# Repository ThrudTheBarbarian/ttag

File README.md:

# ttag
JTAG adapter for the Trion FPGAs. Accepts an FTDI mini-module which saves having to
embed an FTDI chip onto every board.

Exposes the SPI lines for programming SPI flash devices, and the JTAG lines for the FPGA.

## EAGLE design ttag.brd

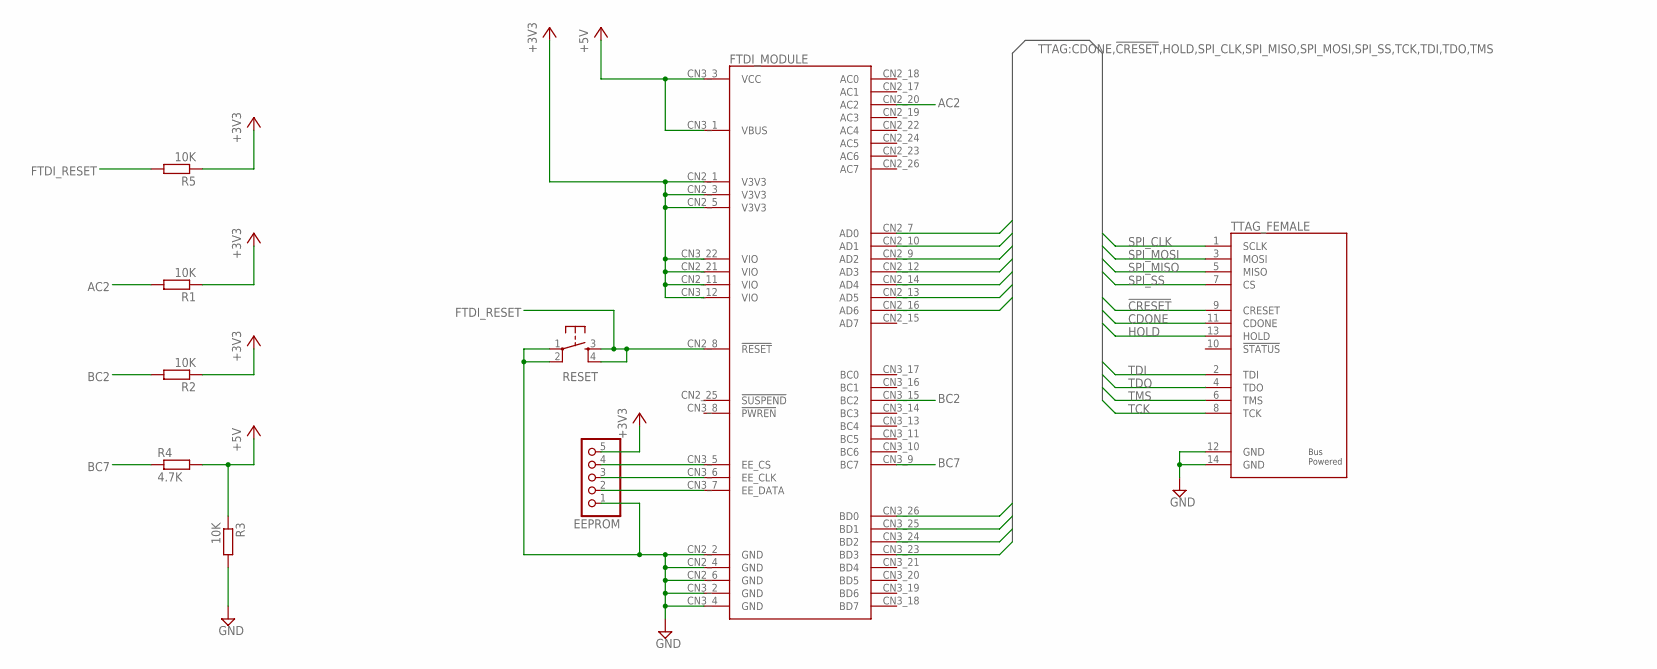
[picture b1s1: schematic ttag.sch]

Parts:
EEPROM: PINHD-1X05_2.54; 1X05
FTDI_MODULE: FTDI_MODULE
R1, R2, R3, R5: 10K; M1206
R4: 4.7K; M1206
RESET: TAC_SWITCHPTH; TACTILE-PTH
TTAG_FEMALE: TTAG_F; SFH11PBPCD07RABK

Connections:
!CRESET!: FTDI_MODULE.CN2_14 (AD4), TTAG_FEMALE.9 (CRESET)
+3V3: EEPROM.5, FTDI_MODULE.CN2_1 (V3V3), FTDI_MODULE.CN2_3 (V3V3), FTDI_MODULE.CN2_5 (V3V3), FTDI_MODULE.CN2_11 (VIO), FTDI_MODULE.CN2_21 (VIO), FTDI_MODULE.CN3_12 (VIO), FTDI_MODULE.CN3_22 (VIO), R1.1, R2.1, R5.1
+5V: FTDI_MODULE.CN3_1 (VBUS), FTDI_MODULE.CN3_3 (VCC), R3.1, R4.2
AC2: FTDI_MODULE.CN2_20 (AC2), R1.2
BC2: FTDI_MODULE.CN3_15 (BC2), R2.2
BC7: FTDI_MODULE.CN3_9 (BC7), R4.1
CDONE: FTDI_MODULE.CN2_13 (AD5), TTAG_FEMALE.11 (CDONE)
FTDI_RESET: FTDI_MODULE.CN2_8 (!RESET!), R5.2, RESET.3, RESET.4
GND: EEPROM.1, FTDI_MODULE.CN2_2 (GND), FTDI_MODULE.CN2_4 (GND), FTDI_MODULE.CN2_6 (GND), FTDI_MODULE.CN3_2 (GND), FTDI_MODULE.CN3_4 (GND), R3.2, RESET.1, RESET.2, TTAG_FEMALE.12 (GND), TTAG_FEMALE.14 (GND)
HOLD: FTDI_MODULE.CN2_16 (AD6), TTAG_FEMALE.13 (HOLD)
unnamed: EEPROM.4, FTDI_MODULE.CN3_5 (EE_CS)
unnamed: EEPROM.3, FTDI_MODULE.CN3_6 (EE_CLK)
unnamed: EEPROM.2, FTDI_MODULE.CN3_7 (EE_DATA)
SPI_CLK: FTDI_MODULE.CN2_7 (AD0), TTAG_FEMALE.1 (SCLK)
SPI_MISO: FTDI_MODULE.CN2_9 (AD2), TTAG_FEMALE.5 (MISO)
SPI_MOSI: FTDI_MODULE.CN2_10 (AD1), TTAG_FEMALE.3 (MOSI)
SPI_SS: FTDI_MODULE.CN2_12 (AD3), TTAG_FEMALE.7 (CS)
TCK: FTDI_MODULE.CN3_26 (BD0), TTAG_FEMALE.8 (TCK)
TDI: FTDI_MODULE.CN3_25 (BD1), TTAG_FEMALE.2 (TDI)
TDO: FTDI_MODULE.CN3_24 (BD2), TTAG_FEMALE.4 (TDO)
TMS: FTDI_MODULE.CN3_23 (BD3), TTAG_FEMALE.6 (TMS)

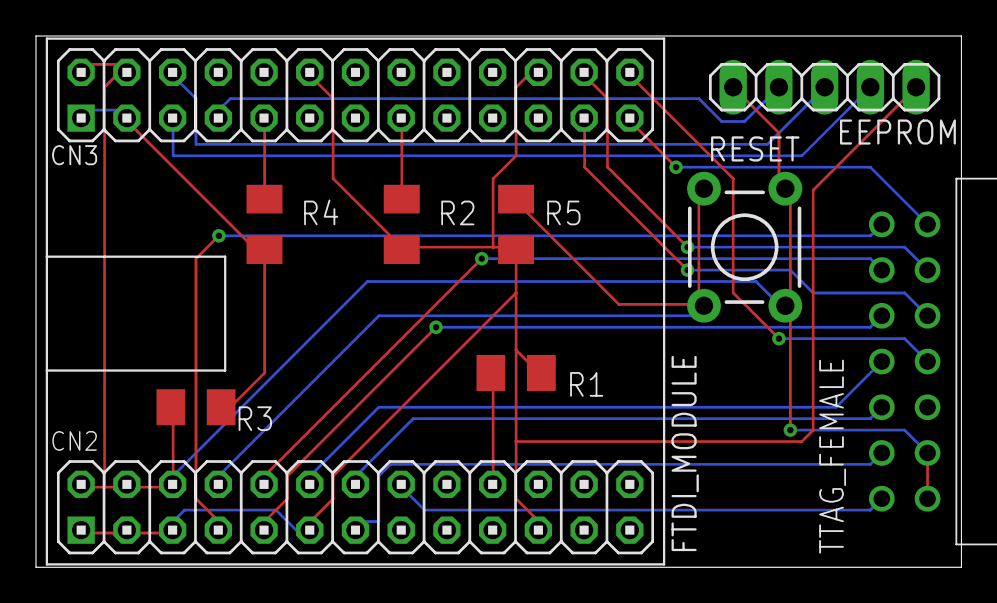
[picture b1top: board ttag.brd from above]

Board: 2 copper layers, 51.4 x 29.5 mm, 9 parts (0 on the bottom side), 21 nets.

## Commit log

2020-11-19 Initial layout etc.

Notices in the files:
parts and their libraries:
SparkFun: Licensing: CC v3.0 Share-Alike You are welcome to use this library for commercial purposes.
